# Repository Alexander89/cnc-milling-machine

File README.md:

# cnc-milling driver for GCode / MCode

This little driver runs on a RPi V 3B+ and is connected to a PCB board to control the steppers.

Until now, a gamepad is required to move the head around and select and start programs.

A Web UI is available on http://<pi>:1506

## RPi connector Board

Eagle drawings and cam files are available in the folder `PCB` (TODO). Reach me out, I still have some PCBs on stock.
(4x V1 bank, 1x V1 assembled and tested, 1x V2 blank)

### Rev1

- end switches inputs
- Dir + Pul outputs
- screw holes

you can use Z-Down end switch input to calibrate

### Rev2

- end switches inputs
- Dir + Pul outputs
- 2 pwm out (servo or GPIO out/in 3.3V!)
- external power input (jumper)
- i²C connector
- calibrate input
- more compact
- screw holes

## Software features

- Support for G0 G1 G2 G3 G21 G90 G91 M0 M1 M3 M4 M5
- Settings file
- Switch spindle on / off
- Motor ramp for speed up
- Web UI for remote control
- Manipulate GCode in UI
- Multi input directory live watcher for USB-Stick detection.
- Show progress in UI
- V1: Responsive web ui for mobile phones

### Bugfix

- **F** is now mm/min. (pref. mm/sec)

## Upcoming features

1. External input as Change Tool (setting external_input_enabled) ( M6 )
2. Move spindel in UI with virtual joystick
3. Better Responsive web ui for mobile phones

backlog

4. Emergency trigger (stop || stop and go up)
5. Drive to max dimensions for selected program
6. Show path in ui
7. Redesign UI and widget System

## supported gCode commands

| code | command                                              | example                                                 |
| ---- | ---------------------------------------------------- | ------------------------------------------------------- |
| G0   | rapid move to XYZ position                           | G0 X1.0 Y0.0 Z 2.0                                      |
| G1   | milling move to XYZ position with F speed            | G0 X1.0 Y1.0 Z -1.0 F1.2                                |
| G2   | CW circle around IJK til XYZ is reached with F speed | G2 I-11.302914 J-5.330242 K0.0 X1.177652 Y5.964921 Z0.0 |
| G3   | CCW G2                                               | G3 I-11.302914 J-5.330242 K0.0 X1.177652 Y5.964921 Z0.0 |
| G21  | unit is mm                                           | G21                                                     |
| G90  | X, Y, Z Absolute                                     | G90                                                     |
| G91  | X, Y, Z Relative                                     | G91                                                     |
| M0   | Switch Off                                           | M0                                                      |
| M1   | Switch Off                                           | M1                                                      |
| M3   | Switch On                                            | M3                                                      |
| M4   | Switch On                                            | M4                                                      |
| M5   | Switch Off                                           | M5                                                      |
| M6   | Change tool (WIP)                                    | M6 T02                                                  |

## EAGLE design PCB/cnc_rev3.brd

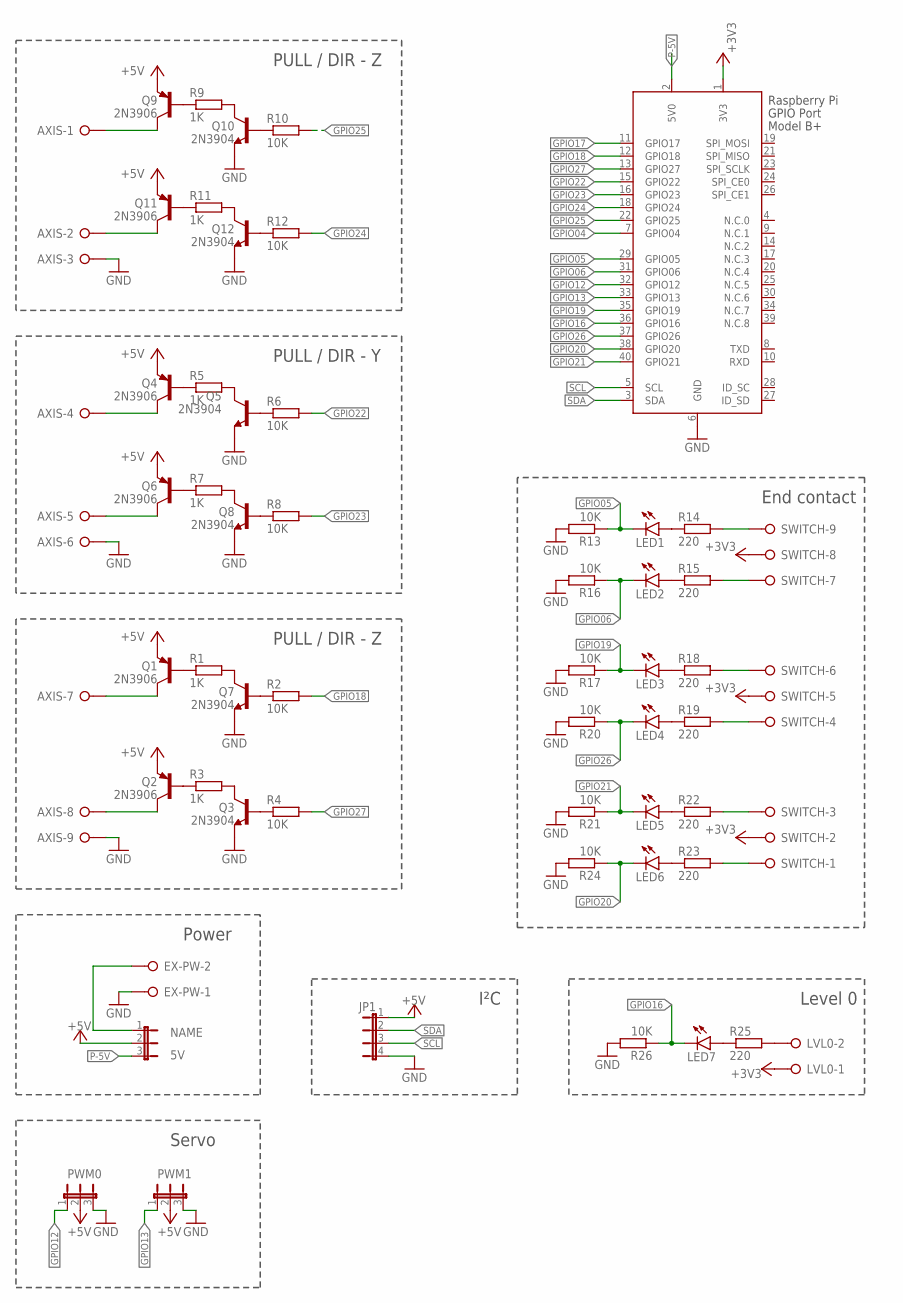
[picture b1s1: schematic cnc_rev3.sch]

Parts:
AXIS: W237-9P
EX-PW: W237-132
JP1: JP4E; JP4
JP_5V: 5V; JP2
LED1, LED2, LED3, LED4, LED5, LED6: LED3MM
LED7: LED3MM
LVL0: W237-02P; W237-132
PWM0, PWM1: JP2E; JP2
Q1, Q2, Q4, Q6, Q9, Q11: 2N3906; TO92
Q3, Q5, Q7, Q8, Q10, Q12: 2N3904; TO92
R1, R3, R5, R7, R9, R11: 1K; 0414V
R2, R4, R6, R8, R10, R12, R13, R16, R17, R20, R21, R24, R26: 10K; 0414V
R14, R15, R18, R19, R22, R23, R25: 220; 0414V
RPI_CONNECT: RASPI_GPIO_B+_BOX
SWITCH: W237-09P; W237-9P

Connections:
+3V3: LVL0.1, RPI_CONNECT.1 (3V3), SWITCH.2, SWITCH.5, SWITCH.8
+5V: JP1.1, JP_5V.2, PWM0.2, PWM1.2, Q1.3 (E), Q2.3 (E), Q4.3 (E), Q6.3 (E), Q9.3 (E), Q11.3 (E)
DIRU: AXIS.8, Q2.1 (C)
DIRX: AXIS.2, Q11.1 (C)
DIRY: AXIS.5, Q6.1 (C)
GND: AXIS.3, AXIS.6, AXIS.9, EX-PW.1, JP1.4, PWM0.3, PWM1.3, Q3.3 (E), Q5.3 (E), Q7.3 (E), Q8.3 (E), Q10.3 (E), Q12.3 (E), R13.2, R16.2, R17.2, R20.2, R21.2, R24.2, R26.2, RPI_CONNECT.6 (GND)
GPIO04: RPI_CONNECT.7 (GPIO04)
GPIO05: LED1.K (C), R13.1, RPI_CONNECT.29 (GPIO05)
GPIO06: LED2.K (C), R16.1, RPI_CONNECT.31 (GPIO06)
GPIO12: PWM0.1, RPI_CONNECT.32 (GPIO12)
GPIO13: PWM1.1, RPI_CONNECT.33 (GPIO13)
GPIO16: LED7.K (C), R26.1, RPI_CONNECT.36 (GPIO16)
GPIO17: RPI_CONNECT.11 (GPIO17)
GPIO18: R2.2, RPI_CONNECT.12 (GPIO18)
GPIO19: LED3.K (C), R17.1, RPI_CONNECT.35 (GPIO19)
GPIO20: LED6.K (C), R24.1, RPI_CONNECT.38 (GPIO20)
GPIO21: LED5.K (C), R21.1, RPI_CONNECT.40 (GPIO21)
GPIO22: R6.2, RPI_CONNECT.15 (GPIO22)
GPIO23: R8.2, RPI_CONNECT.16 (GPIO23)
GPIO24: R12.2, RPI_CONNECT.18 (GPIO24)
GPIO25: R10.2, RPI_CONNECT.22 (GPIO25)
GPIO26: LED4.K (C), R20.1, RPI_CONNECT.37 (GPIO26)
GPIO27: R4.2, RPI_CONNECT.13 (GPIO27)
unnamed: Q1.2 (B), R1.1
unnamed: Q7.1 (C), R1.2
unnamed: Q7.2 (B), R2.1
unnamed: LED7.A, R25.1
unnamed: LVL0.2, R25.2
unnamed: Q4.2 (B), R5.1
unnamed: LED1.A, R14.1
unnamed: Q2.2 (B), R3.1
unnamed: Q3.2 (B), R4.1
unnamed: Q3.1 (C), R3.2
unnamed: Q5.2 (B), R6.1
unnamed: Q5.1 (C), R5.2
unnamed: Q6.2 (B), R7.1
unnamed: Q8.2 (B), R8.1
unnamed: Q8.1 (C), R7.2
unnamed: Q9.2 (B), R9.1
unnamed: Q10.2 (B), R10.1
unnamed: Q10.1 (C), R9.2
unnamed: Q11.2 (B), R11.1
unnamed: Q12.2 (B), R12.1
unnamed: Q12.1 (C), R11.2
unnamed: R14.2, SWITCH.9
unnamed: LED2.A, R15.1
unnamed: R15.2, SWITCH.7
unnamed: LED3.A, R18.1
unnamed: R18.2, SWITCH.6
unnamed: LED4.A, R19.1
unnamed: R19.2, SWITCH.4
unnamed: LED5.A, R22.1
unnamed: R22.2, SWITCH.3
unnamed: LED6.A, R23.1
unnamed: R23.2, SWITCH.1
P-5V: JP_5V.3, RPI_CONNECT.2 (5V0)
P-EXT: EX-PW.2, JP_5V.1
PULU: AXIS.7, Q1.1 (C)
PULY: AXIS.4, Q4.1 (C)
PULZ: AXIS.1, Q9.1 (C)
SCL: JP1.3, RPI_CONNECT.5 (SCL)
SDA: JP1.2, RPI_CONNECT.3 (SDA)

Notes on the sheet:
Level 0
I²C
End contact
Power
Servo
PULL / DIR - Z
PULL / DIR - Y

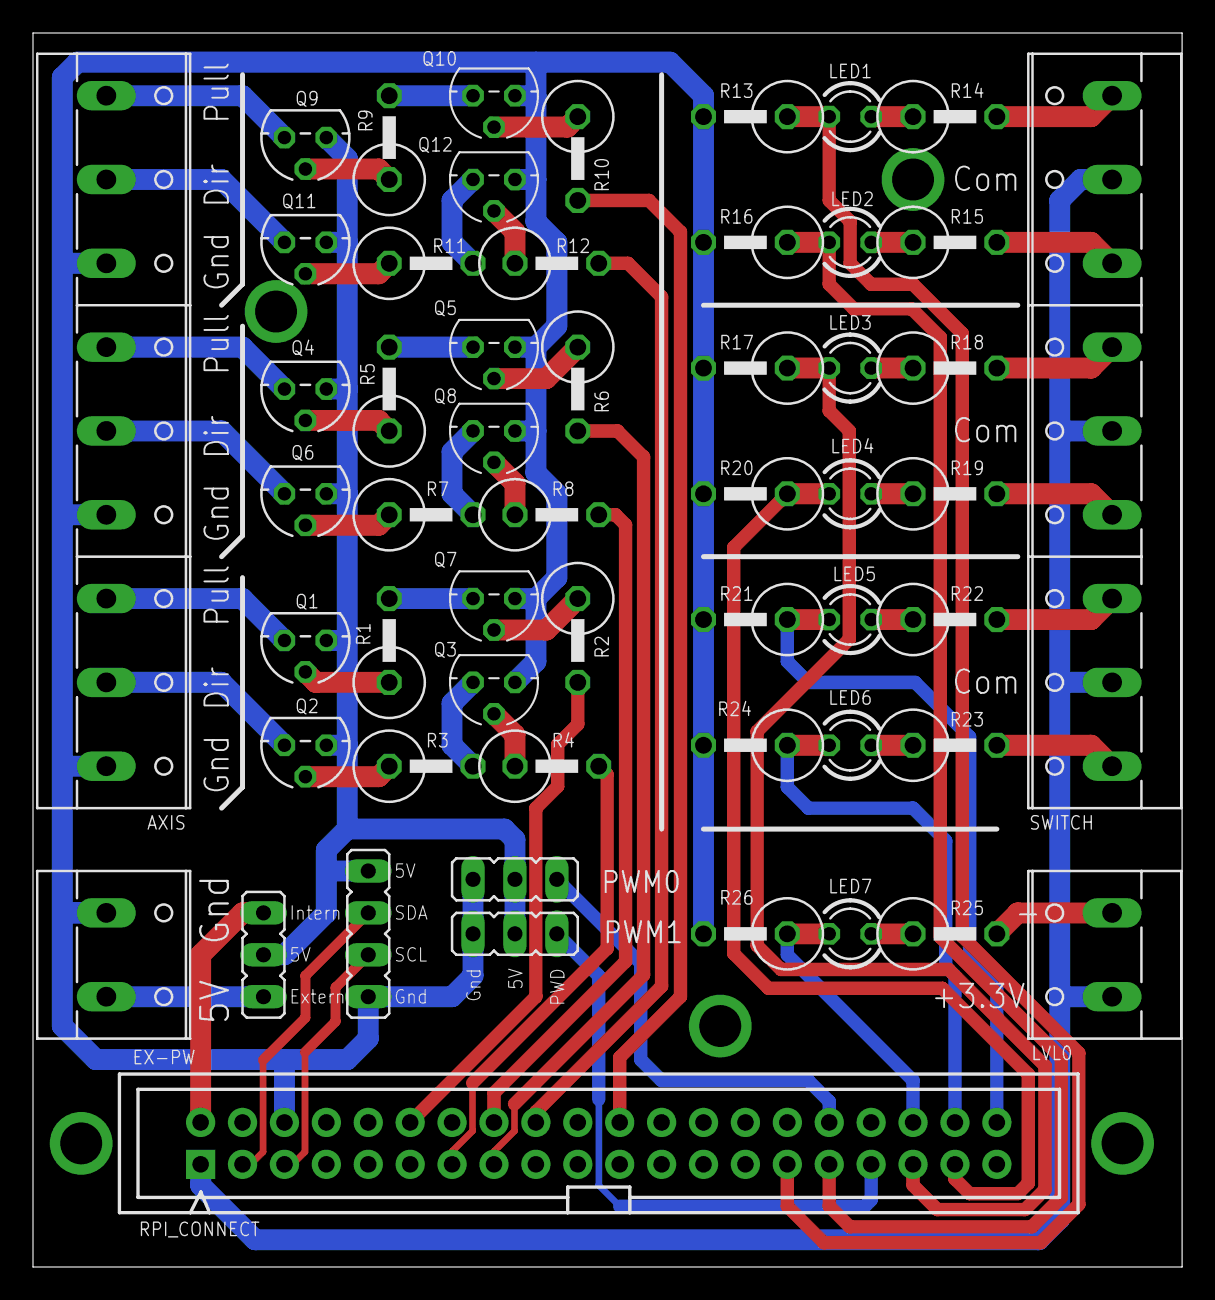
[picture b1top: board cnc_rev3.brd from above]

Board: 2 copper layers, 69.6 x 74.8 mm, 54 parts (0 on the bottom side), 60 nets.

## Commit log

2020-07-05 Low lvl motor driver
2020-07-06 remote
2020-07-09 start progs
2020-07-10 start with programs nr 2
2020-07-15 redesign
2020-07-20 half way sync processes
2020-07-25 atomic management
2020-07-25 stepsize per motor
2020-08-15 add calibration
2020-08-17 nearly done with G2 G3 integration
2020-09-06 pocket
2020-09-06 invert - z function
2020-09-11 calibrated + reset
2020-09-11 G20 + G21
2020-09-11 add readme
2020-09-12 fix ;
2020-10-15 fix speed for programs
2020-10-15 add Eagle files
2020-10-15 cleanup
2020-10-15 first draft for motor ramp
2020-10-17 increase performance
2020-10-17 more cleanup
2020-10-17 impl_manual send for more fluid control
2020-10-17 less examples
2020-10-17 fix cruve again
2021-01-04 ui start
2021-01-05 ui connection init
2021-01-06 iter
2021-01-08 cleanup app
2021-01-08 implement Controller interface and ui Log msg
2021-01-11 ui missing settings
2021-01-12 more UI stuff (redesign, settings)
2021-01-15 ad static support
2021-01-16 more info for prog runtime
2021-01-20 refactor project / motor mod
2021-01-20 refactor main.rs to app
2021-01-20 fix save and more refactoring
2021-01-20 fix save in ui
2021-01-21 move On_off switch to controller_thread add settings, add on_off_delay settings connect to Miscellaneous commands in programs add on_off to UI
2021-01-21 ban settings.yaml
2021-01-21 control new settings with ui
2021-01-21 fix node-forge vulnerabilities
2021-01-23 fit to mobile devices
2021-01-23 fix output + clean up
2021-01-23 clippy
2021-01-25 interchange endswitch when dir invert
2021-02-19 cleanup + clippy
2021-02-19 [WIP] stash
2021-02-19 [WIP] stash - start visualize ramps
2021-02-19 Implement external input into CNC engine
2021-02-19 readme update
2021-02-20 change to mm/min (pref mm/sec), calibrate (min, max, middle), compensate overshooting after motor ramp-up, cleanup
2021-02-24 add acceleration + ui + settings
2021-02-26 rampUp WIP
2021-02-26 lets try
2021-02-28 ui fix
2021-02-28 dump V3
2021-03-08 rework hardware engine
2021-03-09 better Motor control
2021-03-09 implement Control infrastructure
2021-03-11 Bump elliptic from 6.5.3 to 6.5.4 in /ui
    Bumps [elliptic](https://github.com/indutny/elliptic) from 6.5.3 to 6.5.4.
    - [Release notes](https://github.com/indutny/elliptic/releases)
    - [Commits](https://github.com/indutny/elliptic/compare/v6.5.3...v6.5.4)
2021-03-17 change to global event bus and more cleanup
2021-03-17 WIP back to running version
2021-03-17 wip cleanup
2021-05-11 Bump hosted-git-info from 2.8.8 to 2.8.9 in /ui
    Bumps [hosted-git-info](https://github.com/npm/hosted-git-info) from 2.8.8 to 2.8.9.
    - [Release notes](https://github.com/npm/hosted-git-info/releases)
    - [Changelog](https://github.com/npm/hosted-git-info/blob/v2.8.9/CHANGELOG.md)
    - [Commits](https://github.com/npm/hosted-git-info/compare/v2.8.8...v2.8.9)
2021-05-11 Bump lodash from 4.17.20 to 4.17.21 in /ui
    Bumps [lodash](https://github.com/lodash/lodash) from 4.17.20 to 4.17.21.
    - [Release notes](https://github.com/lodash/lodash/releases)
    - [Commits](https://github.com/lodash/lodash/compare/4.17.20...4.17.21)
2021-05-26 Bump browserslist from 4.16.0 to 4.16.6 in /ui
    Bumps [browserslist](https://github.com/browserslist/browserslist) from 4.16.0 to 4.16.6.
    - [Release notes](https://github.com/browserslist/browserslist/releases)
    - [Changelog](https://github.com/browserslist/browserslist/blob/main/CHANGELOG.md)
    - [Commits](https://github.com/browserslist/browserslist/compare/4.16.0...4.16.6)
2021-08-12 Bump path-parse from 1.0.6 to 1.0.7 in /ui
    Bumps [path-parse](https://github.com/jbgutierrez/path-parse) from 1.0.6 to 1.0.7.
    - [Release notes](https://github.com/jbgutierrez/path-parse/releases)
    - [Commits](https://github.com/jbgutierrez/path-parse/commits/v1.0.7)
    ---
    updated-dependencies:
    - dependency-name: path-parse
2022-03-29 Bump minimist from 1.2.5 to 1.2.6 in /ui
    Bumps [minimist](https://github.com/substack/minimist) from 1.2.5 to 1.2.6.
    - [Release notes](https://github.com/substack/minimist/releases)
    - [Commits](https://github.com/substack/minimist/compare/1.2.5...1.2.6)
    ---
    updated-dependencies:
    - dependency-name: minimist
2022-06-06 Bump actix-http from 2.2.0 to 2.2.2
    Bumps [actix-http](https://github.com/actix/actix-web) from 2.2.0 to 2.2.2.
    - [Release notes](https://github.com/actix/actix-web/releases)
    - [Changelog](https://github.com/actix/actix-web/blob/master/CHANGES.md)
    - [Commits](https://github.com/actix/actix-web/compare/http-v2.2.0...http-v2.2.2)
    ---
    updated-dependencies:
2022-06-17 Bump smallvec from 1.6.0 to 1.8.0
    Bumps [smallvec](https://github.com/servo/rust-smallvec) from 1.6.0 to 1.8.0.
    - [Release notes](https://github.com/servo/rust-smallvec/releases)
    - [Commits](https://github.com/servo/rust-smallvec/compare/v1.6.0...v1.8.0)
    ---
    updated-dependencies:
    - dependency-name: smallvec
2022-06-17 Bump thread_local from 1.0.1 to 1.1.4
    Bumps [thread_local](https://github.com/Amanieu/thread_local-rs) from 1.0.1 to 1.1.4.
    - [Release notes](https://github.com/Amanieu/thread_local-rs/releases)
    - [Commits](https://github.com/Amanieu/thread_local-rs/compare/v1.0.1...1.1.4)
    ---
    updated-dependencies:
    - dependency-name: thread_local
2022-11-10 Bump minimatch from 3.0.4 to 3.1.2 in /ui
    Bumps [minimatch](https://github.com/isaacs/minimatch) from 3.0.4 to 3.1.2.
    - [Release notes](https://github.com/isaacs/minimatch/releases)
    - [Commits](https://github.com/isaacs/minimatch/compare/v3.0.4...v3.1.2)
    ---
    updated-dependencies:
    - dependency-name: minimatch
2022-12-07 Bump decode-uri-component from 0.2.0 to 0.2.2 in /ui
    Bumps [decode-uri-component](https://github.com/SamVerschueren/decode-uri-component) from 0.2.0 to 0.2.2.
    - [Release notes](https://github.com/SamVerschueren/decode-uri-component/releases)
    - [Commits](https://github.com/SamVerschueren/decode-uri-component/compare/v0.2.0...v0.2.2)
    ---
    updated-dependencies:
    - dependency-name: decode-uri-component
2022-12-12 Bump qs from 6.5.2 to 6.5.3 in /ui
    Bumps [qs](https://github.com/ljharb/qs) from 6.5.2 to 6.5.3.
    - [Release notes](https://github.com/ljharb/qs/releases)
    - [Changelog](https://github.com/ljharb/qs/blob/main/CHANGELOG.md)
    - [Commits](https://github.com/ljharb/qs/compare/v6.5.2...v6.5.3)
    ---
    updated-dependencies:
2023-01-07 Bump json5 from 1.0.1 to 1.0.2 in /ui
    Bumps [json5](https://github.com/json5/json5) from 1.0.1 to 1.0.2.
    - [Release notes](https://github.com/json5/json5/releases)
    - [Changelog](https://github.com/json5/json5/blob/main/CHANGELOG.md)
    - [Commits](https://github.com/json5/json5/compare/v1.0.1...v1.0.2)
    ---
    updated-dependencies:
2023-01-20 Bump bumpalo from 3.4.0 to 3.12.0
    Bumps [bumpalo](https://github.com/fitzgen/bumpalo) from 3.4.0 to 3.12.0.
    - [Release notes](https://github.com/fitzgen/bumpalo/releases)
    - [Changelog](https://github.com/fitzgen/bumpalo/blob/main/CHANGELOG.md)
    - [Commits](https://github.com/fitzgen/bumpalo/compare/3.4.0...3.12.0)
    ---
    updated-dependencies:
